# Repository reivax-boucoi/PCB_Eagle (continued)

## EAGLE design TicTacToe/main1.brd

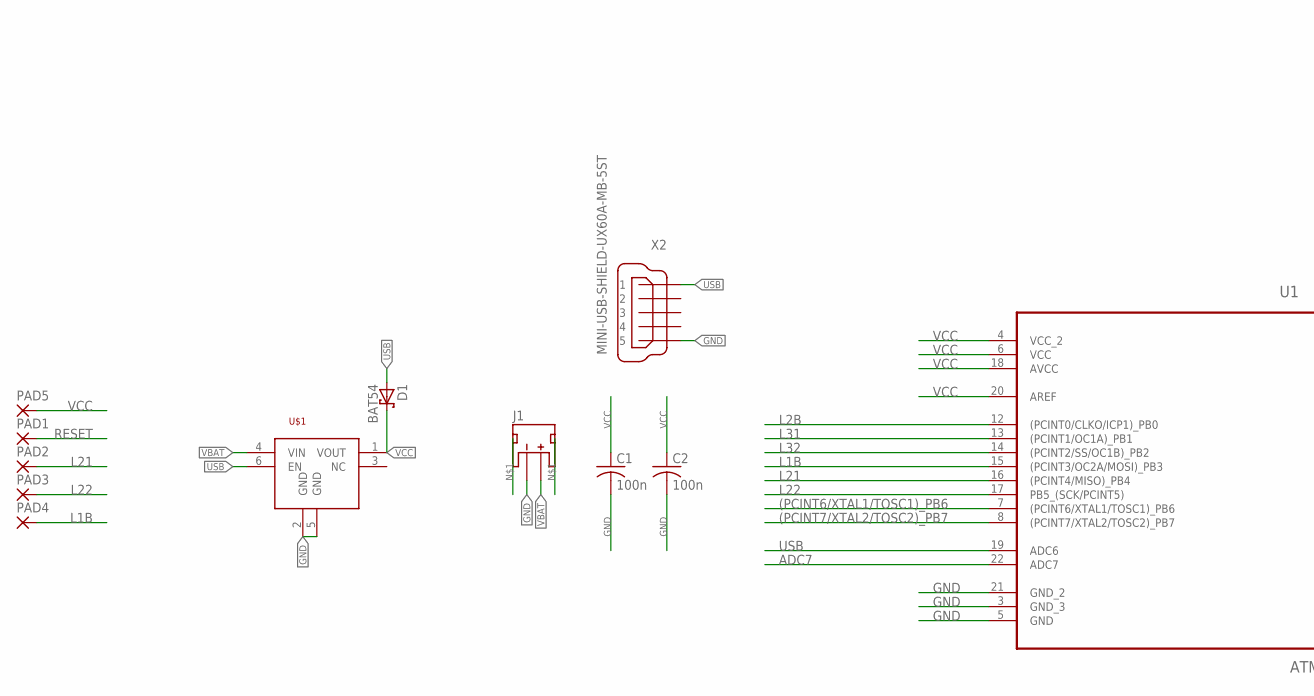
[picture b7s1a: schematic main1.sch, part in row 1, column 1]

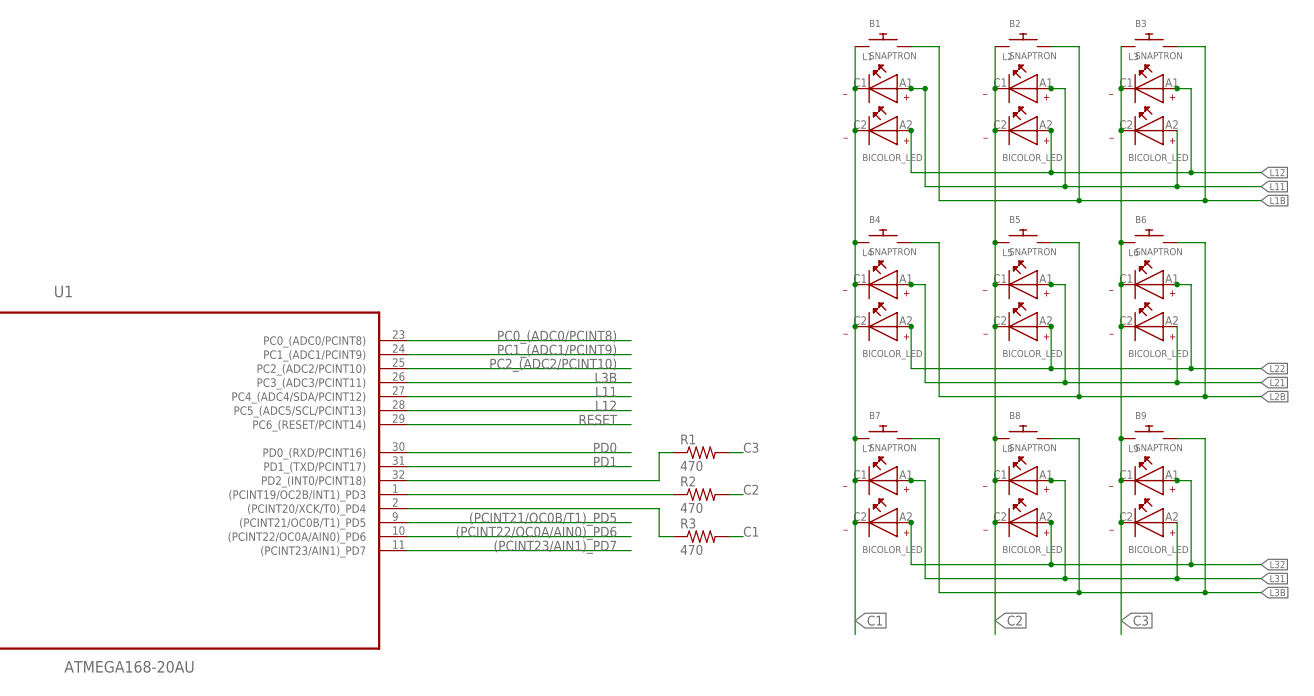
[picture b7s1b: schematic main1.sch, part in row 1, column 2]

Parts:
B1, B2, B3, B4, B5, B6, B7, B8, B9: SNAPTRON; SNAPTRON-8.5
C1, C2: 100n; C0603
D1: BAT54; SOT23
J1: JST_2MM_MALE; JST-2-SMD
L1, L2, L3, L4, L5, L6, L7, L8, L9: BICOLOR_LED
PAD1, PAD5: SMD2; SMD1,27-2,54
PAD2, PAD3, PAD4: SMD5; SMD2,54-5,08
R1, R2, R3: 470; R0603
U1: ATMEGA168-20AU; QFP80P900X900X120-32N
U$1: MIC94090; SC70-6L
X2: MINI-USB-SHIELD-UX60A-MB-5ST; UX60A-MB-5ST

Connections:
(PCINT6/XTAL1/TOSC1)_PB6: U1.7 ((PCINT6/XTAL1/TOSC1)_PB6)
(PCINT7/XTAL2/TOSC2)_PB7: U1.8 ((PCINT7/XTAL2/TOSC2)_PB7)
(PCINT21/OC0B/T1)_PD5: U1.9 ((PCINT21/OC0B/T1)_PD5)
(PCINT22/OC0A/AIN0)_PD6: U1.10 ((PCINT22/OC0A/AIN0)_PD6)
(PCINT23/AIN1)_PD7: U1.11 ((PCINT23/AIN1)_PD7)
ADC7: U1.22 (ADC7)
C1: B1.P$1, B4.P$1, B7.P$1, L1.C1, L1.C2, L4.C1, L4.C2, L7.C1, L7.C2, R3.2
C2: B2.P$1, B5.P$1, B8.P$1, L2.C1, L2.C2, L5.C1, L5.C2, L8.C1, L8.C2, R2.2
C3: B3.P$1, B6.P$1, B9.P$1, L3.C1, L3.C2, L6.C1, L6.C2, L9.C1, L9.C2, R1.2
GND: C1.2, C2.2, J1.1 (-), U1.3 (GND_3), U1.5 (GND), U1.21 (GND_2), U$1.2 (GND), U$1.5 (GND), X2.5
L1B: B1.P$2, B2.P$2, B3.P$2, PAD4.1, U1.15 ((PCINT3/OC2A/MOSI)_PB3)
L2B: B4.P$2, B5.P$2, B6.P$2, U1.12 ((PCINT0/CLKO/ICP1)_PB0)
L3B: B7.P$2, B8.P$2, B9.P$2, U1.26 (PC3_(ADC3/PCINT11))
L11: L1.A1, L2.A1, L3.A2, U1.27 (PC4_(ADC4/SDA/PCINT12))
L12: L1.A2, L2.A2, L3.A1, U1.28 (PC5_(ADC5/SCL/PCINT13))
L21: L4.A1, L5.A1, L6.A2, PAD2.1, U1.16 ((PCINT4/MISO)_PB4)
L22: L4.A2, L5.A2, L6.A1, PAD3.1, U1.17 (PB5_(SCK/PCINT5))
L31: L7.A1, L8.A1, L9.A2, U1.13 ((PCINT1/OC1A)_PB1)
L32: L7.A2, L8.A2, L9.A1, U1.14 ((PCINT2/SS/OC1B)_PB2)
unnamed: J1.NC1 (PAD1), J1.NC2 (PAD2)
unnamed: R2.1, U1.1 ((PCINT19/OC2B/INT1)_PD3)
unnamed: R3.1, U1.2 ((PCINT20/XCK/T0)_PD4)
unnamed: R1.1, U1.32 (PD2_(INT0/PCINT18))
PC0_(ADC0/PCINT8): U1.23 (PC0_(ADC0/PCINT8))
PC1_(ADC1/PCINT9): U1.24 (PC1_(ADC1/PCINT9))
PC2_(ADC2/PCINT10): U1.25 (PC2_(ADC2/PCINT10))
PD0: U1.30 (PD0_(RXD/PCINT16))
PD1: U1.31 (PD1_(TXD/PCINT17))
RESET: PAD1.1, U1.29 (PC6_(RESET/PCINT14))
USB: D1.1 (A), U1.19 (ADC6), U$1.6 (EN), X2.1
VBAT: J1.2 (+), U$1.4 (VIN)
VCC: C1.1, C2.1, D1.3 (C), PAD5.1, U1.4 (VCC_2), U1.6 (VCC), U1.18 (AVCC), U1.20 (AREF), U$1.1 (VOUT)

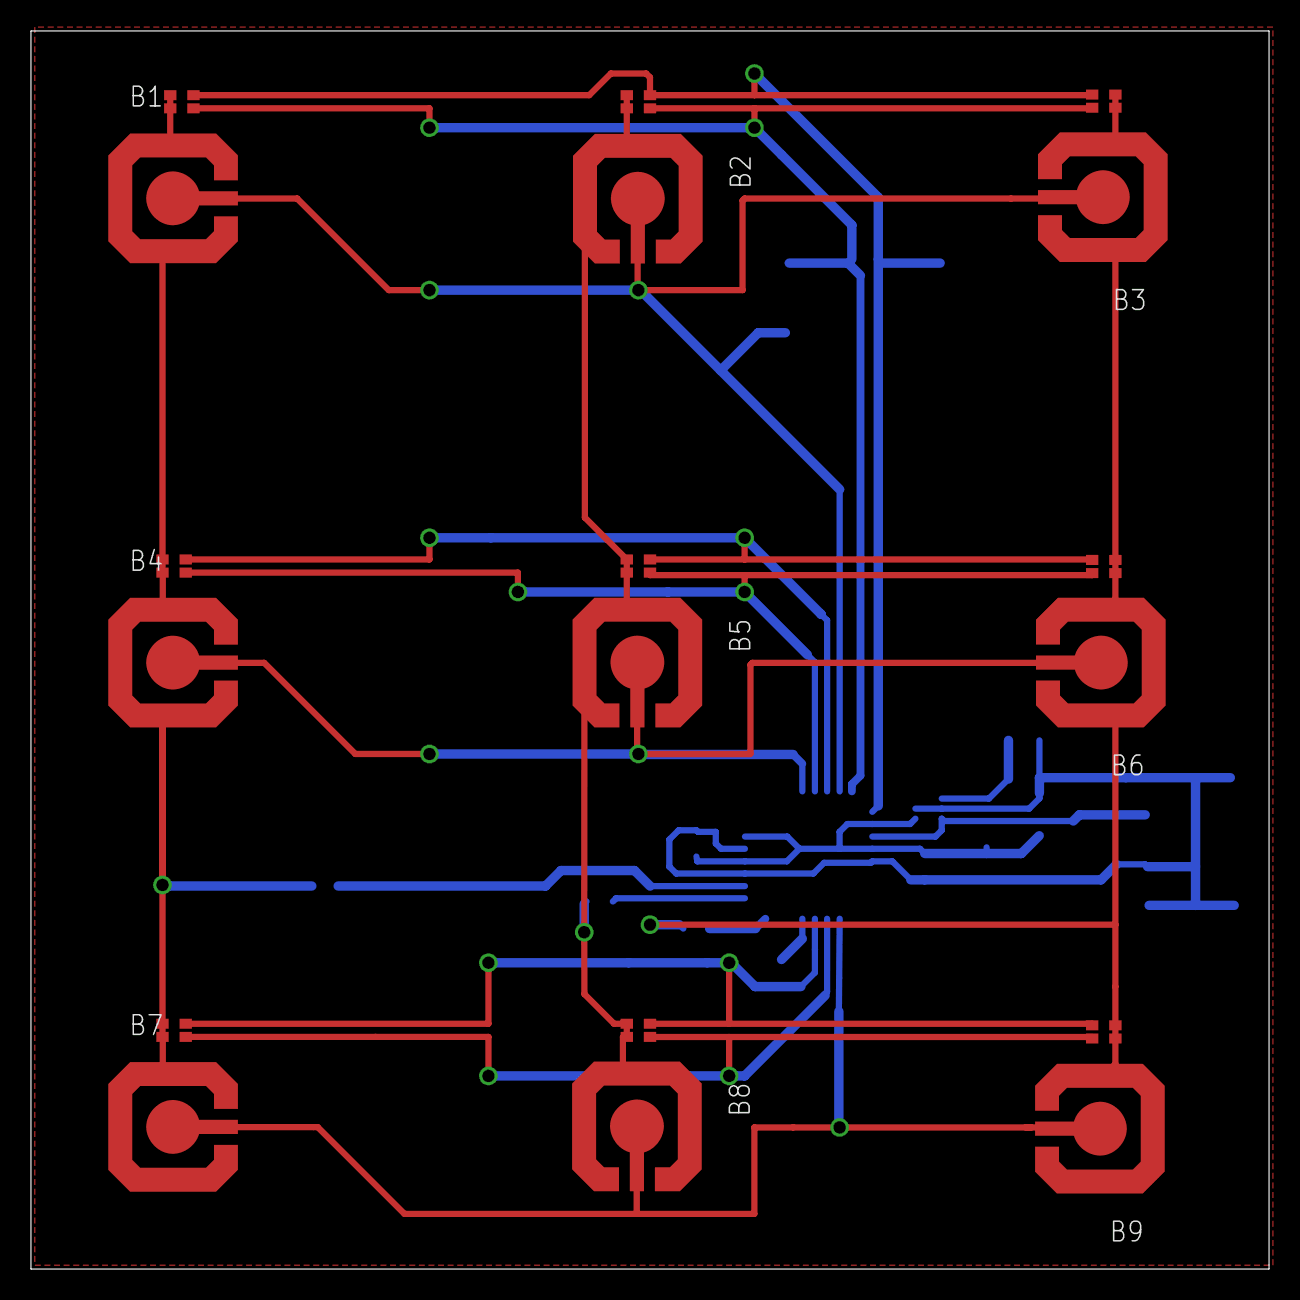
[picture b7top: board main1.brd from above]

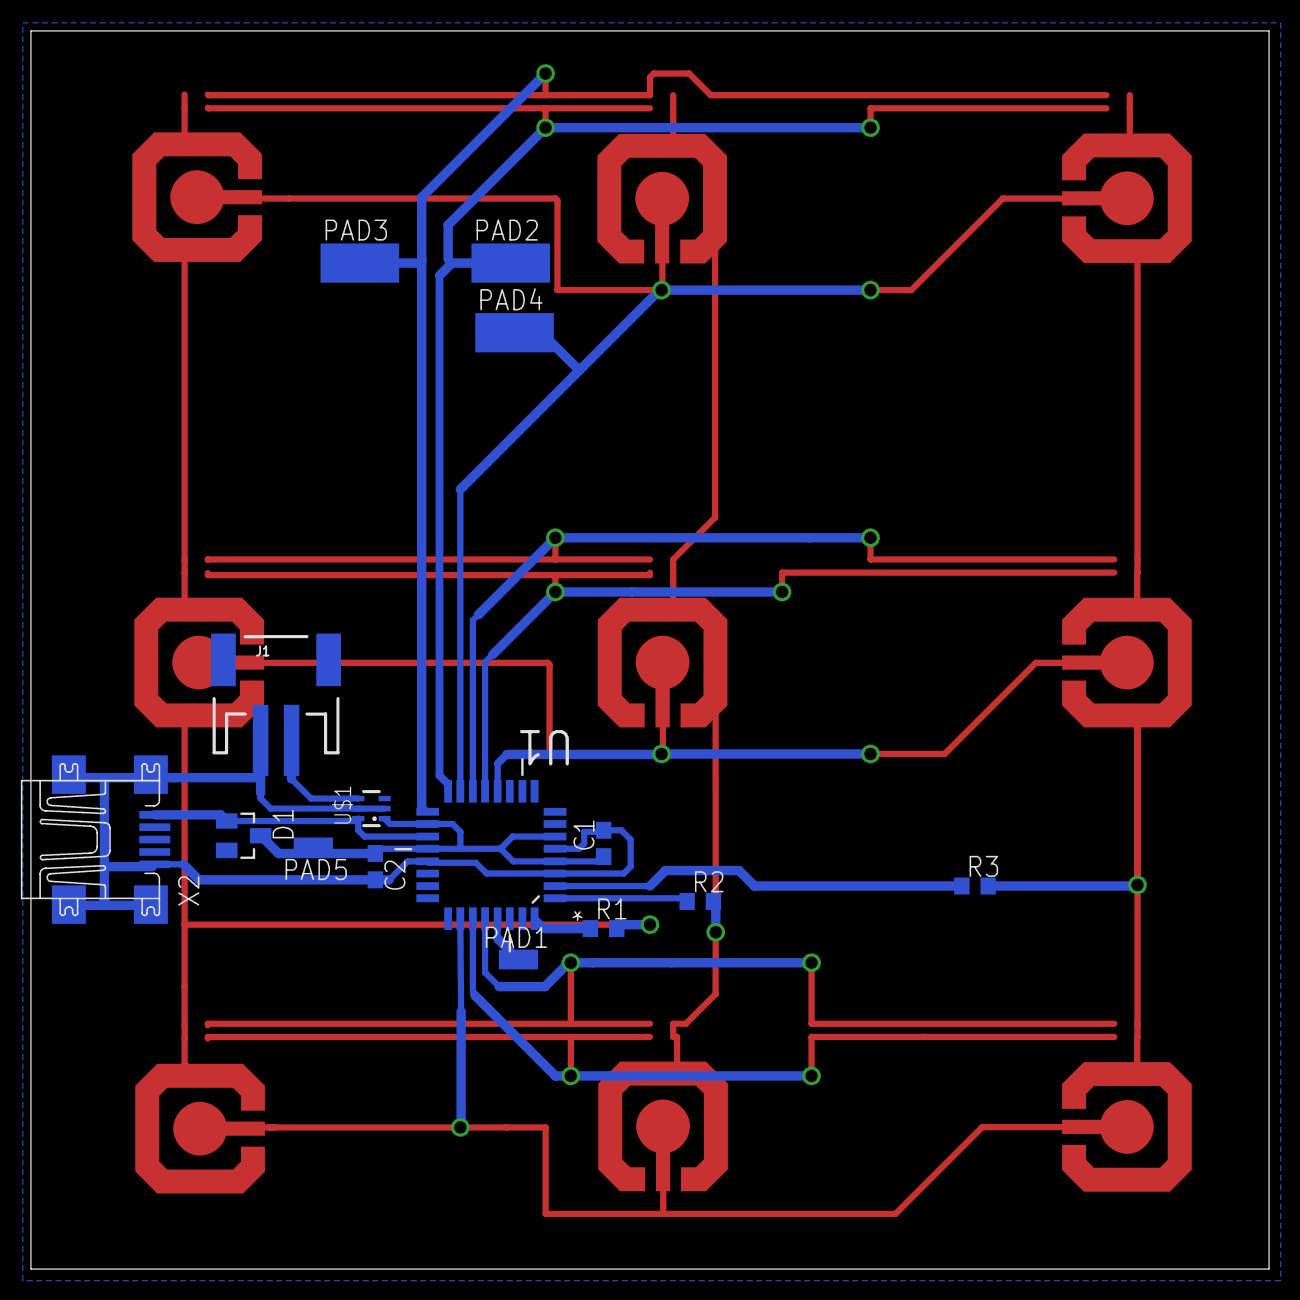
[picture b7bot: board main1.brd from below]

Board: 2 copper layers, 80.0 x 80.0 mm, 33 parts (15 on the bottom side), 21 nets.

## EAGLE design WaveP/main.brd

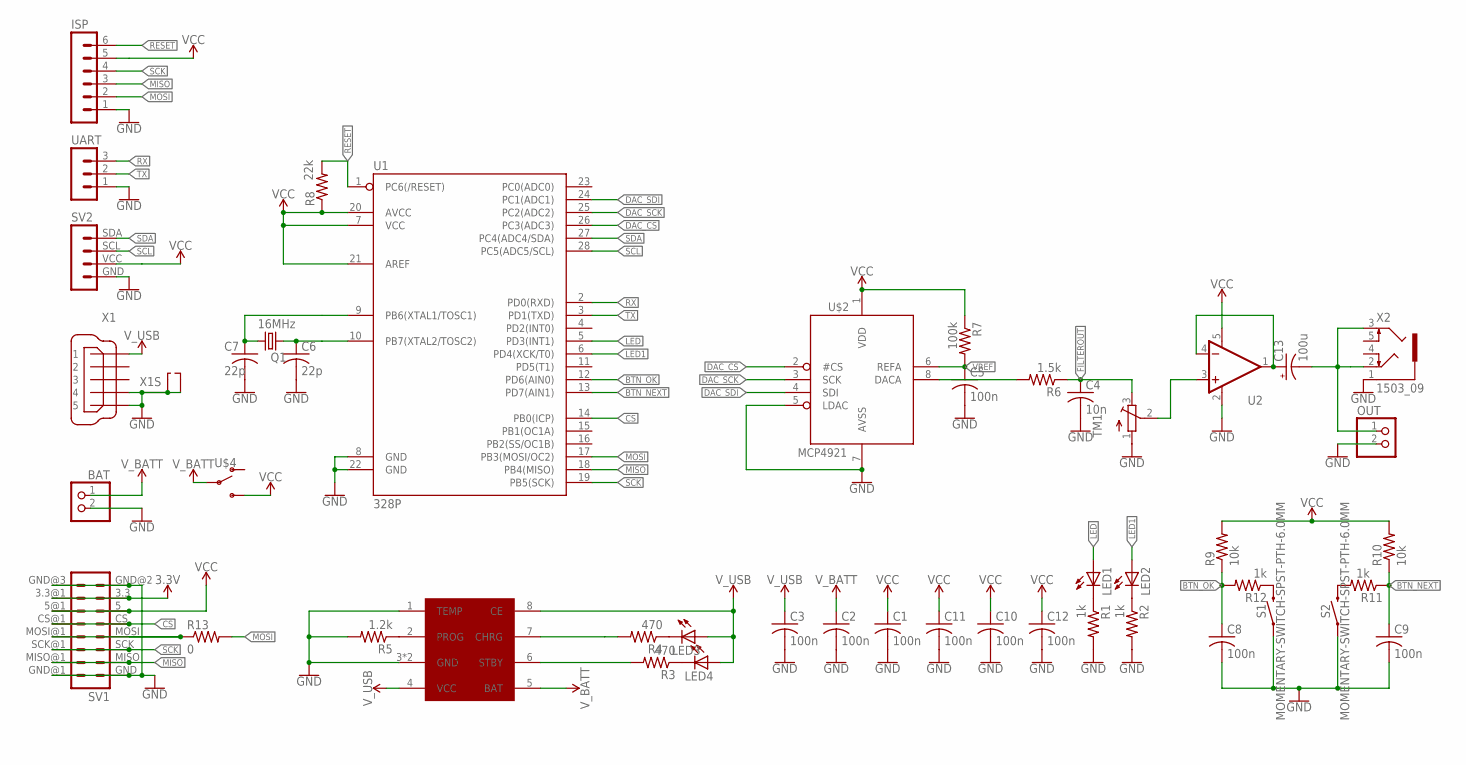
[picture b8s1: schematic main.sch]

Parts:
BAT: PINHD-1X2; 1X02
C1, C2, C3, C5, C8, C9, C10, C11, C12: 100n; C0603
C4: 10n; C0603
C6, C7: 22p; C0603
C13: 100u; E2,5-6E
CH1: TP4056; SOP8
ISP: MA06-1
LED1, LED2, LED3, LED4: LED3MM
OUT: PINHD-1X2; 1X02
Q1: 16MHz; HC49/S
R1, R2, R11, R12: 1k; R0603
R3, R4: 470; R0603
R5: 1.2k; R0603
R6: 1.5k; R0603
R7: 100k; R0603
R8: 22k; R0603
R9, R10: 10k; R0603
R13: 0; 0204/5
S1, S2: MOMENTARY-SWITCH-SPST-PTH-6.0MM; TACTILE_SWITCH_PTH_6.0MM
SV1: SD_CARD
SV2: OLED
TM1: TRIMPOT3386; TRIM-3386
U1: 328P; DIP28
U2: MCP6291T; SOT23-5
U$2: MCP4921; DIL08
U$4: PC_SPDT_SWITCH
UART: MA03-1
X1: MINI-USB_SHIELD5P2-32005-601; 32005-601
X2: 1503_09

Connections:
3.3V: SV1.3.3, SV1.3.3@1 (3.3)
BTN_NEXT: C9.1, R10.1, R11.1, U1.13 (PD7(AIN1))
BTN_OK: C8.1, R9.1, R12.2, U1.12 (PD6(AIN0))
CS: SV1.CS, SV1.CS@1 (CS), U1.14 (PB0(ICP))
DAC_CS: U1.26 (PC3(ADC3)), U$2.2 (#CS)
DAC_SCK: U1.25 (PC2(ADC2)), U$2.3 (SCK)
DAC_SDI: U1.24 (PC1(ADC1)), U$2.4 (SDI)
FILTEROUT: C4.1, R6.1, TM1.3 (E)
GND: BAT.2, C1.2, C2.2, C3.2, C4.2, C5.2, C6.2, C7.2, C8.2, C9.2, C10.2, C11.2, C12.2, CH1.1 (TEMP), CH1.3 (GND), CH1.9 (GND), ISP.1, OUT.2, R1.2, R2.2, R5.2, S1.1, S2.1, SV1.GND, SV1.GND@1 (GND), SV1.GND@2 (GND), SV1.GND@3 (GND), SV2.GND, TM1.1 (A), U1.8 (GND), U1.22 (GND), U2.2 (V-), U$2.5 (LDAC), U$2.7 (AVSS), UART.1, X1.4, X1.5, X1.M1 (S1), X1.M2 (S2), X2.1
LED: LED1.A, U1.5 (PD3(INT1))
LED1: LED2.A, U1.6 (PD4(XCK/T0))
MISO: ISP.3, SV1.MISO, SV1.MISO@1 (MISO), U1.18 (PB4(MISO))
MOSI: ISP.2, R13.2, U1.17 (PB3(MOSI/OC2))
N1: R13.1, SV1.MOSI, SV1.MOSI@1 (MOSI)
unnamed: R6.2, U$2.8 (DACA)
unnamed: C13.+, U2.1 (OUT), U2.4 (-IN)
unnamed: LED3.K (C), R4.1
unnamed: LED4.K (C), R3.1
unnamed: CH1.2 (PROG), R5.1
unnamed: CH1.7 (CHRG), R4.2
unnamed: CH1.6 (STBY), R3.2
unnamed: LED2.K (C), R2.1
unnamed: LED1.K (C), R1.1
unnamed: C13.-, OUT.1, X2.2, X2.3
unnamed: TM1.2 (S), U2.3 (+IN)
unnamed: R11.2, S2.3 (2)
unnamed: R12.1, S1.3 (2)
PB6(XTAL1/TOSC1): C7.1, Q1.1, U1.9 (PB6(XTAL1/TOSC1))
PB7(XTAL2/TOSC2): C6.1, Q1.2, U1.10 (PB7(XTAL2/TOSC2))
RESET: ISP.6, R8.2, U1.1 (PC6(/RESET))
RX: U1.2 (PD0(RXD)), UART.3
SCK: ISP.4, SV1.SCK, SV1.SCK@1 (SCK), U1.19 (PB5(SCK))
SCL: SV2.SCL, U1.28 (PC5(ADC5/SCL))
SDA: SV2.SDA, U1.27 (PC4(ADC4/SDA))
TX: U1.3 (PD1(TXD)), UART.2
VCC: C1.1, C10.1, C11.1, C12.1, ISP.5, R7.1, R8.1, R9.2, R10.2, SV1.5, SV1.5@1 (5), SV2.VCC, U1.7 (VCC), U1.20 (AVCC), U1.21 (AREF), U2.5 (V+), U$2.1 (VDD), U$4.NO
VREF: C5.1, R7.2, U$2.6 (REFA)
V_BATT: BAT.1, C2.1, CH1.5 (BAT), U$4.COM
V_USB: C3.1, CH1.4 (VCC), CH1.8 (CE), LED3.A, LED4.A, X1.1

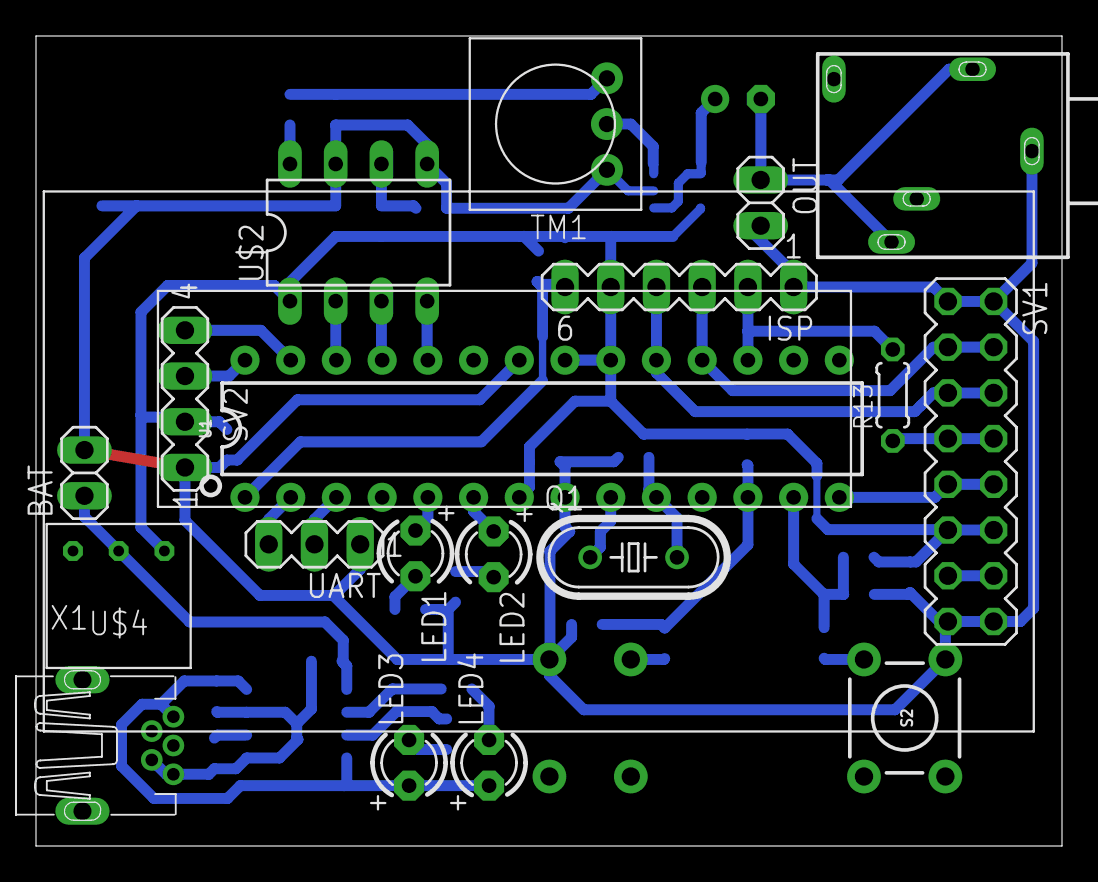
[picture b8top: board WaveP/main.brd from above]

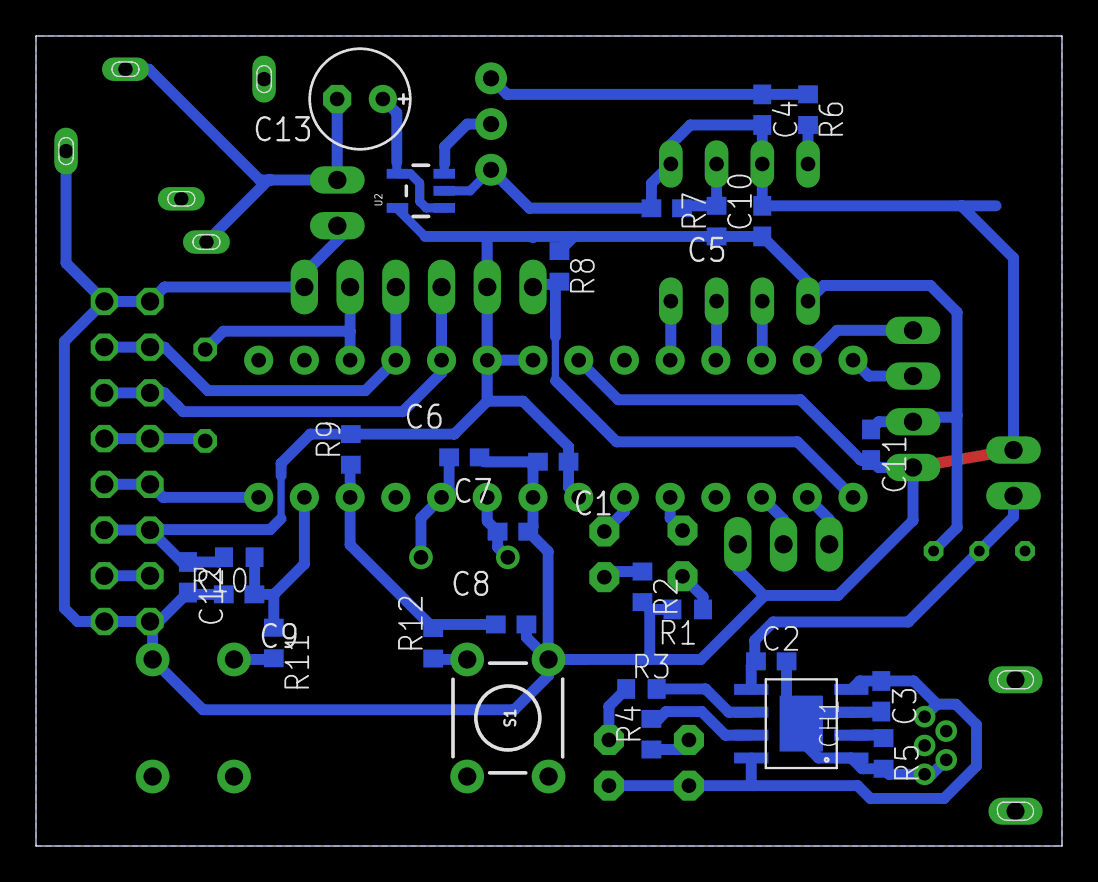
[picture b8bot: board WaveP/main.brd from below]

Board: 2 copper layers, 57.0 x 45.0 mm, 47 parts (28 on the bottom side), 39 nets.
